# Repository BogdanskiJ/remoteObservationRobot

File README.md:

# Remote Observation Robot

## Project description

This project presents a remote observation robot that was designed and built by me from scratch in 2018. This robot allows the user to conduct remote observations in hard-to-reach places, which is particularly useful in applications such as exploration of uninhabited areas, industrial inspections or environmental monitoring.

## Functions

### 1. HD camera

The robot is equipped with an HD camera that allows you to obtain high-quality images and recordings in real time. The user can conveniently view the image from the camera on their device.

### 2. Remote Control

The robot is remotely controlled using a dedicated application or web interface. Thanks to this, the user can control the robot's movement and camera orientation.

### 3. Systems 

- 2 x Arduino (Arduino Uno in my case)
- Wifi Camera
- Transmitter and receiver modules
- Motors and wheels for movement
- Distance sensors
- Battery or power source
- Computer or mobile device for remote control

### 4. Source Files

Source files allow you to recreate the robot using programs such as: Arduino IDE, 123D Design Autocad, EAGLE, Eclipse.

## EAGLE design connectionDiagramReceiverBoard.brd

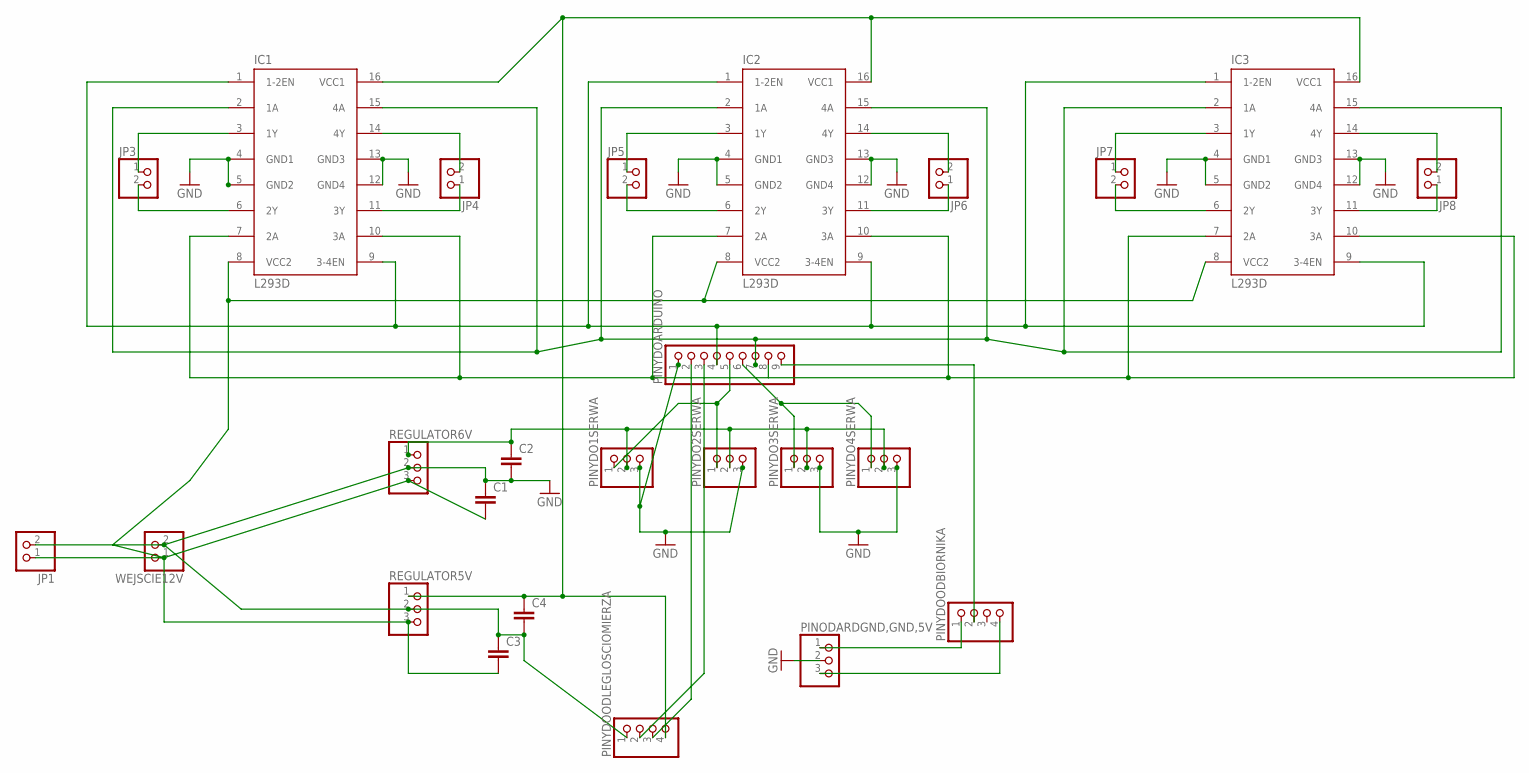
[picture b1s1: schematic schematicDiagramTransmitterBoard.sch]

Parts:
C1, C2, C3, C4: C2,5-3; C2.5-3
IC1, IC2, IC3: L293D; DIL16
JP1, JP3, JP4, JP5, JP6, JP7, JP8: PINHD-1X2; 1X02
PINODARDGND,GND,5V: PINHD-1X3; 1X03
PINYDO1SERWA, PINYDO2SERWA, PINYDO3SERWA, PINYDO4SERWA: PINHD-1X3; 1X03
PINYDOARDUINO: PINHD-1X9; 1X09
PINYDOODBIORNIKA: PINHD-1X4; 1X04
PINYDOODLEGLOSCIOMIERZA: PINHD-1X4; 1X04
REGULATOR5V, REGULATOR6V: PINHD-1X3; 1X03
WEJSCIE12V: PINHD-1X2; 1X02

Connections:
GND: C1.1, C2.2, C3.1, C4.2, IC1.4 (GND1), IC1.5 (GND2), IC1.12 (GND4), IC1.13 (GND3), IC2.4 (GND1), IC2.5 (GND2), IC2.12 (GND4), IC2.13 (GND3), IC3.4 (GND1), IC3.5 (GND2), IC3.12 (GND4), IC3.13 (GND3), JP1.2, PINODARDGND,GND,5V.2, PINYDO1SERWA.3, PINYDO2SERWA.3, PINYDO3SERWA.3, PINYDO4SERWA.3, PINYDOARDUINO.1, PINYDOODLEGLOSCIOMIERZA.1, REGULATOR5V.2, REGULATOR6V.2, WEJSCIE12V.2
unnamed: C1.2, C3.2, IC1.8 (VCC2), IC2.8 (VCC2), IC3.8 (VCC2), JP1.1, REGULATOR5V.3, REGULATOR6V.3, WEJSCIE12V.1
unnamed: C2.1, PINYDO1SERWA.2, PINYDO2SERWA.2, PINYDO3SERWA.2, PINYDO4SERWA.2, REGULATOR6V.1
unnamed: C4.1, IC1.16 (VCC1), IC2.16 (VCC1), IC3.16 (VCC1), PINYDOODLEGLOSCIOMIERZA.4, REGULATOR5V.1
unnamed: IC1.14 (4Y), JP4.2
unnamed: IC1.11 (3Y), JP4.1
unnamed: IC1.6 (2Y), JP3.2
unnamed: IC1.3 (1Y), JP3.1
unnamed: IC2.3 (1Y), JP5.1
unnamed: IC2.6 (2Y), JP5.2
unnamed: IC2.14 (4Y), JP6.2
unnamed: IC2.11 (3Y), JP6.1
unnamed: IC3.3 (1Y), JP7.1
unnamed: IC3.6 (2Y), JP7.2
unnamed: IC3.14 (4Y), JP8.2
unnamed: IC3.11 (3Y), JP8.1
unnamed: PINODARDGND,GND,5V.1, PINYDOODBIORNIKA.1
unnamed: PINODARDGND,GND,5V.3, PINYDOODBIORNIKA.4
unnamed: PINYDOARDUINO.3, PINYDOODLEGLOSCIOMIERZA.2
unnamed: PINYDOARDUINO.2, PINYDOODLEGLOSCIOMIERZA.3
unnamed: IC1.1 (1-2EN), IC1.9 (3-4EN), IC2.1 (1-2EN), IC2.9 (3-4EN), IC3.1 (1-2EN), IC3.9 (3-4EN), PINYDOARDUINO.4
unnamed: IC1.7 (2A), IC1.10 (3A), IC2.7 (2A), IC2.10 (3A), IC3.7 (2A), IC3.10 (3A), PINYDOARDUINO.8
unnamed: IC1.2 (1A), IC1.15 (4A), IC2.2 (1A), IC2.15 (4A), IC3.2 (1A), IC3.15 (4A), PINYDOARDUINO.7
unnamed: PINYDO1SERWA.1, PINYDO2SERWA.1, PINYDOARDUINO.5
unnamed: PINYDOARDUINO.9, PINYDOODBIORNIKA.2
unnamed: PINYDO3SERWA.1, PINYDO4SERWA.1, PINYDOARDUINO.6

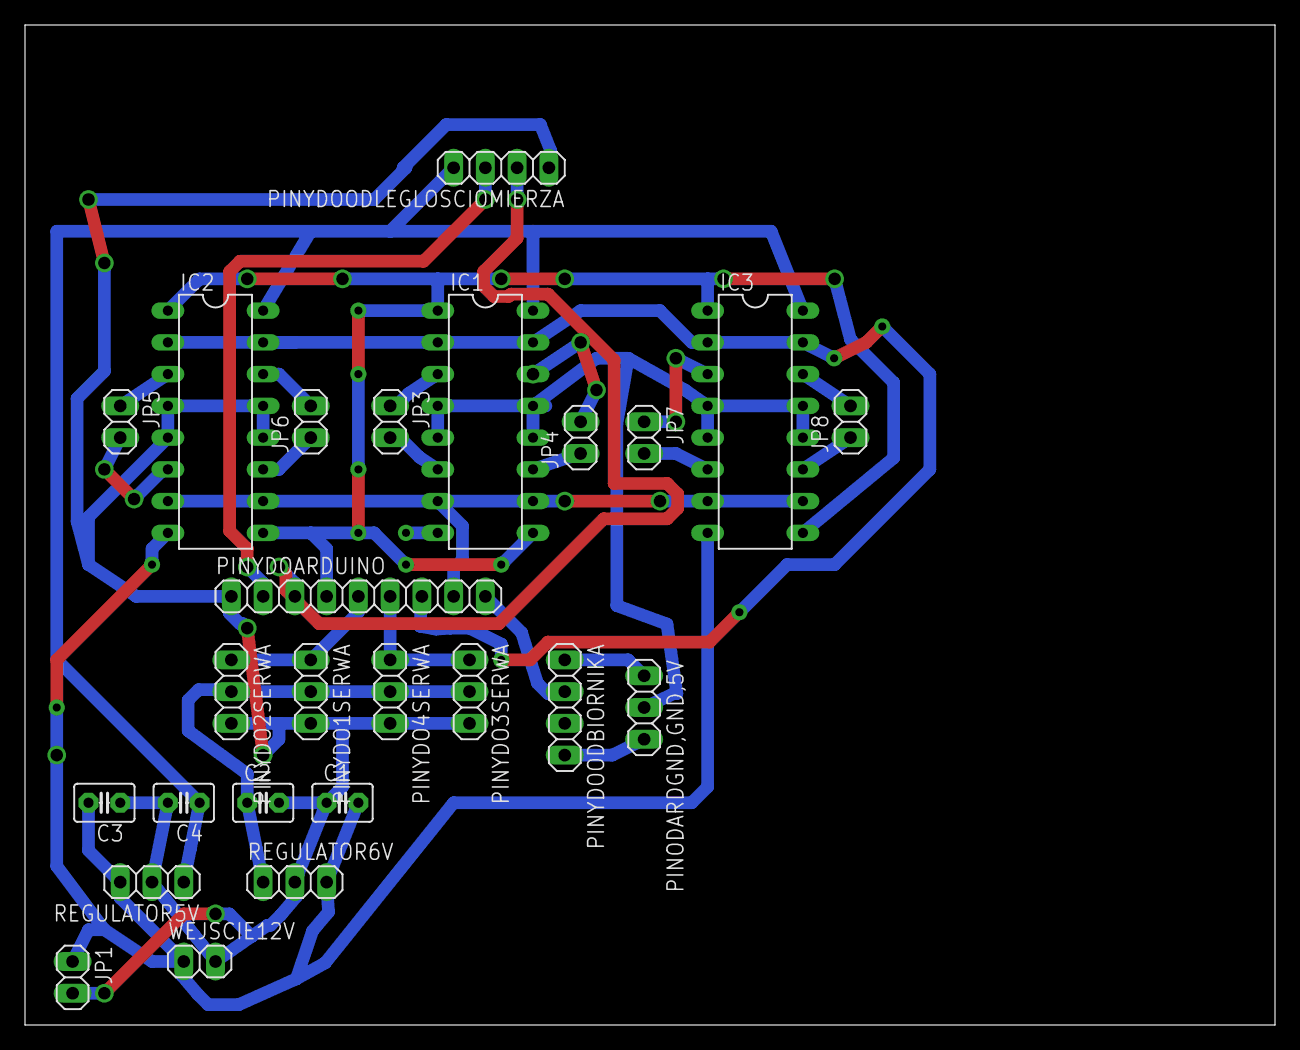
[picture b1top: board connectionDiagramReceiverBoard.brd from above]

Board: 2 copper layers, 100.0 x 80.0 mm, 25 parts (0 on the bottom side), 26 nets.

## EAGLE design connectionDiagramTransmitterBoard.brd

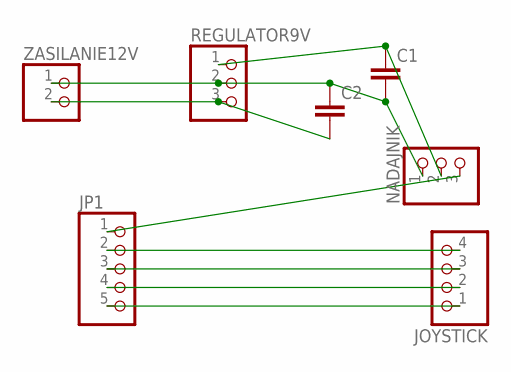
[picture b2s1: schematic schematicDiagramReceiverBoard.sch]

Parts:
C1, C2: C2,5-3; C2.5-3
JOYSTICK: PINHD-1X4; 1X04
JP1: PINHD-1X5; 1X05
NADAJNIK: PINHD-1X3; 1X03
REGULATOR9V: PINHD-1X3; 1X03
ZASILANIE12V: PINHD-1X2; 1X02

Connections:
unnamed: C1.2, C2.1, NADAJNIK.1, REGULATOR9V.2, ZASILANIE12V.1
unnamed: C2.2, REGULATOR9V.3, ZASILANIE12V.2
unnamed: JOYSTICK.1, JP1.5
unnamed: JOYSTICK.2, JP1.4
unnamed: JOYSTICK.3, JP1.3
unnamed: JOYSTICK.4, JP1.2
unnamed: JP1.1, NADAJNIK.3
unnamed: C1.1, NADAJNIK.2, REGULATOR9V.1

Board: 2 copper layers, 7 parts (0 on the bottom side), 8 nets, no tracks yet.
